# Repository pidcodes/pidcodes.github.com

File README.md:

# pid.codes

Website for [pid.codes](http://pid.codes)

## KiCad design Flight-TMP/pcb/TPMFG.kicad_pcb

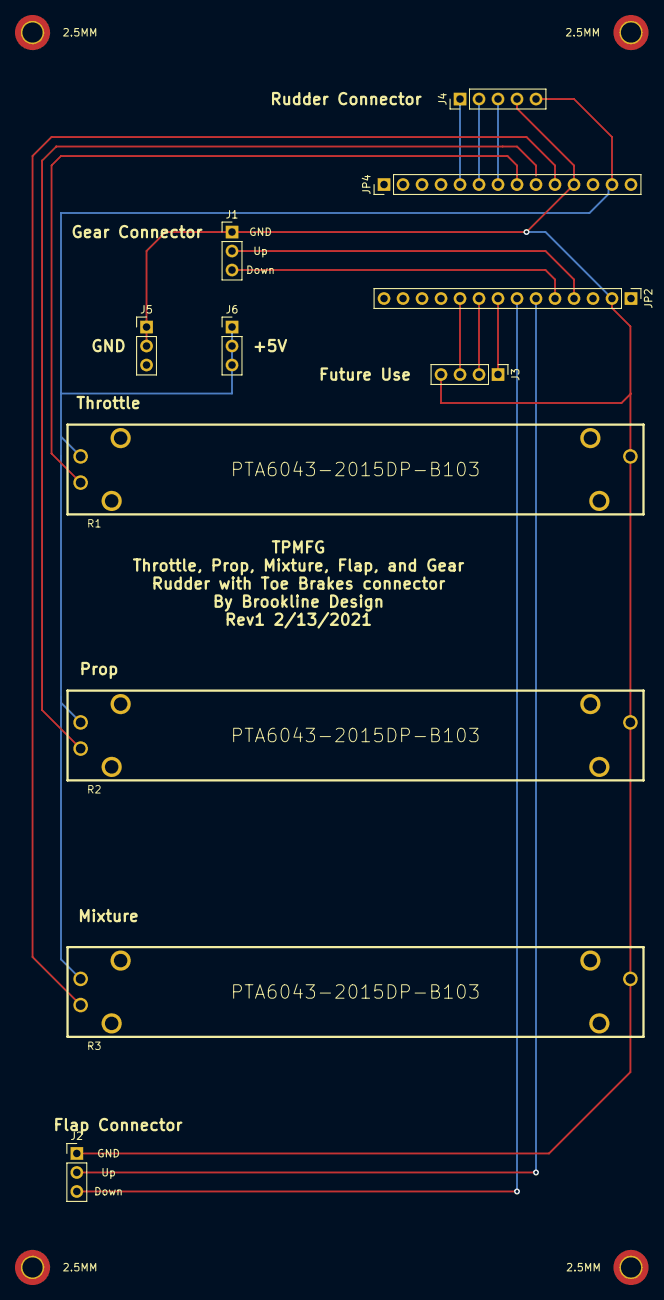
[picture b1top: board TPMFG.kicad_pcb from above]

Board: 2 copper layers, 15 parts (0 on the bottom side), 15 nets.

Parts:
2.5MM, 2.5MM , 2.5MM#2, 2.5MM#3: MountingHole_2.7mm_M2.5_DIN965_Pad_TopBottom
J1, J2: 61300311121; PinHeader_1x03_P2.54mm_Vertical
J3: 0022232041; PinHeader_1x04_P2.54mm_Vertical
J4: B5B-XH-A_LF__SN_; PinHeader_1x05_P2.54mm_Vertical
J5, J6: 640456-3; PinHeader_1x03_P2.54mm_Vertical
JP2, JP4: HEADER-1X14; PinHeader_1x14_P2.54mm_Vertical
R1, R2, R3: PTA6043-2015DP-B103

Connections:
+5V: J4.5, J6.1, J6.2, J6.3, JP4.13, R1.1, R2.1, R3.1
/A3: J4.3, JP4.7
/A4: J4.2, JP4.6
/A5: J4.1, JP4.5
/D5: J3.3, JP2.10
/D7: J3.2, JP2.9
/D9: J3.1, JP2.8
/D10: J2.3, JP2.7
/D11: J2.2, JP2.6
/D12: J1.3, JP2.5
/D13: J1.2, JP2.4
A0: JP4.10, R3.2
A1: JP4.9, R2.2
A2: JP4.8, R1.2
GND: J1.1, J2.1, J3.4, J4.4, J5.1, J5.2, J5.3, JP2.2, JP4.11, R1.3, R2.3, R3.3

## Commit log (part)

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2025-12-06 register 1209/53A0 for the "Diskomator" by 0x53A (Lukas Rieger)
2025-12-06 Update index.md with firmware and Circuitpython links
    Added links to Ai-On-The-Edge-Device firmware and Circuitpython.
2025-12-07 Definition of molnarkares org and 4520 PID
2025-12-07 Added Solderpad license to cover HW
2025-12-07 Adding Diva Engineering and devices
2025-12-08 Request to add 1209:2305 for a CH32V305-based USB High-Speed WS2812B multi-output driver.
2025-12-11 Added organization for tcsenpai and EMPHarvest PID code
2025-12-11 updated the request to a new PID
2025-12-12 0x1209: add 0xBB07 PID (BloomBoot)
2025-12-12 update PID
2025-12-12 Bump actions/cache from 4 to 5
    Bumps [actions/cache](https://github.com/actions/cache) from 4 to 5.
    - [Release notes](https://github.com/actions/cache/releases)
    - [Changelog](https://github.com/actions/cache/blob/main/RELEASES.md)
    - [Commits](https://github.com/actions/cache/compare/v4...v5)
    ---
    updated-dependencies:
2025-12-15 Added PID of 1066 for the Domesday Duplicator project
2025-12-15 Fixed incorred VID -> now 2347
2025-12-15 Added PID of 2347 for the Domesday Duplicator project
2025-12-16 Create index.md
    Add Infinite USB Test organization entry
2025-12-16 Create index.md
    Add PID entry for Generic USB HID Controller
2025-12-19 Clarify source files and licensing requirements
    Clarified prerequisites for project submissions, including licensing requirements and added a note about commercial use starting in 2026.
2025-12-21 Modify title for 2AF4
2025-12-21 Add new PID 2AEE, 2AEF, 2AF0, 2AF1, 2AF7
2025-12-23 Update readme syntax for diva-eng
    Remove unnecessary layout and site information.
2025-12-25 Adding PIDs for WeAct Studio RP2350A Core Boards
    Adding PIDs for WeAct Studio RP2350A Core Boards
2025-12-26 PID request for MegaWiFi Programmer V
2025-12-27 Register picolume org and PID 1209:2008
2026-01-02 Update: Added entries for Pounamu Electronics RE_SWC PID request
2026-01-04 Update index.md
    Fix typo in firmware link
2026-01-04 PID request for IRMP_PICO
2026-01-06 Add org: daylily
2026-01-06 Add PID: c9c9
2026-01-06 Allocate 1209:2640 for a ppm-to-uinput joystick driver
2026-01-07 added link to firmware branch
2026-01-08 Request for 1209:6404 for YAPicoprobe
2026-01-08 Create index.md for SparkType documentation
    Added documentation for SparkType project.
2026-01-08 Create metadata for SparkType Keystroke Injector
    Added project metadata and description for SparkType Keystroke Injector.
2026-01-08 Adicionar metadata para o SparkType Keystroke Injector
2026-01-09 add 42A0
2026-01-10 Create index.md for ZeyBack project
    Added project details and contact information for ZeyBack.
2026-01-10 Add index.md for ZeyBack R2RDAC project
2026-01-10 Create index.md for ZeyBack R2RDAC project
    Added project metadata and description for ZeyBack R2RDAC.
    https://github.com/ERDALECE/ZeyBack
2026-01-10 Add initial index.md for ZeyBack project
2026-01-10 Add index.md for ZeyBack project documentation
    https://github.com/ERDALECE/ZeyBack
2026-01-10 Add initial layout for ZeyBack R2RDAC project
    https://github.com/ERDALECE/ZeyBack
2026-01-10 Add initial configuration for ZeyBack R2RDAC
    ZeyBack R2RDAC
    Open-source DIY audio hardware/firmware project (STM32H743 + FPGA), USB Audio Class 2.0 and native DSD focused.
2026-01-10 Create index.md for ZeyBack R2RDAC project
    Added project details for ZeyBack R2RDAC.
2026-01-10 Change owner name to match casing
2026-01-10 Fix owner casing in index.md
2026-01-11 Add org 'hi0t' and PID 1209:FFCA 'fcart'
2026-01-19 add FF07
2026-01-19 Request PID D500 for Densha de GO PnP controller mod
2026-01-20 asdasdas
2026-01-20 fixing error
2026-01-22 Remove 1209/AFDD This project was superseded and cancelled before any hardware was released. I do not wish to horde PIDs unnecessarily.
2026-01-24 1209:8816
2026-02-02 0x1209: add 0x2119 PID (Firmament-Autopilot)
2026-02-02 Add org information for 2119
2026-02-03 Add 0xB008
2026-02-03 Add bootloader id
2026-02-04 Request PID 0x88BF for Custom RAW HID protocol for macropad keypads
2026-02-05 Added TinyCircuits org
2026-02-05 Added Thumby pid 3500
2026-02-05 Added Thumby Color pid 3501
2026-02-05 Remove commercial change
2026-02-05 Remove trailing space
2026-02-05 Add second PID (2009) for PicoLume Remote, update 2008 for Receiver
    Split single PID registration into two: 0x2008 for the PicoLume
    Receiver and 0x2009 for the PicoLume Remote, as recommended by
    maintainer review.
2026-02-07 add EliaChiarucci org and pid 2715 for DA15 project
2026-02-07 change pid request
2026-02-10 Create index.md for PewPew uGame-S3
2026-02-11 Add CBUnmanned
    Allocate PID 5750
2026-02-11 Add CircuitPython references
2026-02-12 Clarify source files and licensing requirements (#1134)
    * Clarify source files and licensing requirements
    Clarified prerequisites for project submissions, including licensing requirements and added a note about commercial use starting in 2026.
    * Remove commercial change
    * Remove trailing space
2026-02-12 Add project information to info.txt
2026-02-12 Rename info.txt to info.md
2026-02-12 Rename info.md to index.md
2026-02-12 Create index.md for CustomSimEchoSystem project
    Add index.md for CustomSimEchoSystem documentation
2026-02-12 Change layout type from 'pid' to 'org'
2026-02-15 Add PostalPoint Barcode Scanner 1209:A003
2026-02-19 Update index.md
    Fix incorrect owner field
2026-02-20 Add PID B2A8 for Blue2Joy
2026-03-03 added PID for hermes
2026-03-10 1209/BBD1, an ESP32-S3 BLE-HID serial bridge
2026-03-11 Add CoreOrbits Gamerpad VID 1209 PID 2027
2026-03-13 added PID FDFD and new org FutilityDesigns
2026-03-16 Request PIDs f540 and f542 for One ROM
    Request PIDs f540 and f541 for One ROM
    Request PIDs f540 and f542 for One ROM
2026-03-17 add vicharak and pid for shrike
2026-03-21 Create index.md for Jacob Waters profile
    Add personal profile for Jacob Waters with layout and site link.
2026-03-21 Create index.md for Macro Pad project
    Added initial documentation for the Macro Pad project.
2026-03-24 Request PID 1010
2026-03-24 Request PID 5A5A
2026-03-24 Add MixlarLabs index page with metadata
2026-03-24 Add index.md for Mixlar Mix project
2026-03-24 Fix metadata formatting and update site URL
    Corrected the owner casing and updated the site URL to use HTTP.
2026-03-24 Fix owner case: MixlarLabs
2026-03-24 Fix org index.md: remove leading whitespace
2026-04-02 add scd31 org and rcade display adapter
2026-04-03 Add Woyta org and PID 0x5750 for Woyta-Pad macropad
2026-04-09 PID request for Loopian::QUBIT
2026-04-10 Add FF08
2026-04-18 Add 1209/B17E: Aftertone Brume
2026-04-21 Add CyberFly Keyboard (PID 0xCF01)
    Register PID 1209:CF01 for the CyberFly BLE mechanical keyboard,
    an open-source nRF52840-based keyboard running ZMK firmware.
    Add org entry for eggfly.
2026-04-21 Fix source URL: bufferfly_zmk -> cyberfly_zmk
2026-04-21 Fix: nRF52840 is used as bare IC, not a module
2026-04-22 Add Infinite organization
    Add index.md for Infinite project documentation
2026-04-22 Add PID 5390 Electric Controller Base
    Added documentation for Electric Controller Base firmware.
2026-04-22 Add PID 5391 Hybrid Controller Base
    Add initial documentation for Hybrid Controller Base firmware.
2026-04-22 Add PID 5392 Diesel Controller Base
    Add documentation for Diesel Controller Base firmware.
2026-04-22 Add PID 5393 Steam Controller Base
    Add documentation for Steam Controller Base firmware.
2026-04-22 Create index.md for Infinite project
    Add index.md for Infinite project documentation
2026-04-26 Add PID B747
2026-04-28 Add hardware link to index.md
2026-04-28 Update title of USB CDC-ACM Device documentation
    Title changed
2026-04-28 Update index.md
    Title changed
2026-04-29 update the pid name from shrike to shrike-lite
2026-04-30 New request for a pid - Barrier USB
2026-05-01 Add Lectrobox org and PID 0x71C4 (LectroTIC-4 Pulse Timestamper)
2026-05-02 Add PID E502 for KERIgoKBD v2
2026-05-02 Fix PID E501 description
2026-05-02 Added LenweSaralonde organization and BA55 Product ID for Musician MIDI Pico Translator
2026-05-05 Create index.md for USB-I2C Bridge Board
2026-05-06 D9D0: Finomnis: Busylight
2026-05-11 Neubras - OpenReader Config Standard (ORCS) aims to standardize the configuration of USB card readers. The VID/PID is necessary for the software to identify the device in compatible configuration mod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
2026-05-11 Add a request for PID DCB1
2026-05-13 Add Nick Spiker org and 1209:4665 ferros
2026-05-15 Add 1209/9210 Mimic X (kunichiko)
2026-05-16 fix: LGDXRobot2 links
2026-05-17 fix: update link for LGDXRobot
2026-05-18 Request PID A5B3
2026-05-18 fix: add org directory for badjeff
2026-05-20 Add 1209/8500 SteFly Stick Remote - and 8501 for the bootloader port
2026-05-22 Assign 7c88 to match CATS harware id
2026-05-22 Add 1209:4D4D for Matosic Macropad
2026-06-01 Add pid 2641 (volume knob) to oddbit.com org
2026-06-09 Request PID 2833 for Phantomdrive.
2026-06-21 Add PID A2B2 for LibreBridge - Mini
2026-06-23 Rename project from Busylight to BusyBeacon
2026-06-26 Allocate PID 0xF1C0 for AMOVLAB Flycore
